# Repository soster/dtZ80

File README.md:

# dtZ80 - A simple 8 Bit Computer based on the Z80 CPU

This started as a project during the second Corona lockdown, where I had to much free time.
I wanted to design my own 8 Bit computer and decided to use the Z80 CPU.
The first idea was to use a MOS 6502 because a variant of that powers the C64, a computer I used much in my childhood.
The Z80 is easier to source where I live so I used that instead.

I started on breadboards but quickly discovered the limits of that so I soldered some prototypes and finally designed some PCBs with kicad.

The bus is compatible to the Bus of the [RC2014 Z80 computer](https://rc2014.co.uk/), so I can exchange expansion cards.

This documentation now covers the new "Black Edition" of the dtZ80 (Rev 1), a larger board without the need to use extension cards. Previous prototypes had a common bus board and extension cards for the CPU, RAM etc. All software for the previous prototypes can be found at `asm/prototype` for historical reasons.

The dtZ80 uses a Z80 CPU with clocked with 7.3728 Mhz (which doubles as a clock for serial communication), a Z80 SIO for serial communication, a CTC counter timer, 32kb of RAM and 32kb of ROM and a AY-3-8910A sound chip. It uses a single seven segment display for debugging purposes and a 4 line, 20 characters per line LCD for text output.

## Tools

* [rasm](https://github.com/mkoloberdin/rasm) is used as the assembler.
* [Visual Studio Code](https://code.visualstudio.com/) is used as an editor and enviroment for assembler
* [Minipro](https://gitlab.com/DavidGriffith/minipro/) is used to flash the EEPROMs, the hardware is a TL866 II PLUS
* [ticks](https://github.com/z88dk/z88dk) from the z88dk project is used as an emulator / simulator
* A usb to ttl converter for serial communication (can be switched to 5V levels, only needs TX and RX)

## Images

### Address Space

Address lines are assigned by a 74LS138 IC (U6) which activates
or deactivates the correct ICs.

    $00: I/O port 7 segment (A0-A7=0)
    $04: LCD command I/O port (A5=1)
    $05: LCD data I/O port (A5=1,A0=1)
    $40: SIO Data Channel A
    $42: SIO Control Channel A
    $60: CTC Channel 0
    $61: CTC Channel 1
    $62: CTC Channel 2
    $63: CTC Channel 3
    $80: Sound Register
    $81: Sound Data

#### LCD

The black edition uses a 4 line, 20 column LCD Display (2004A V1.1) probably based on the HD44780 Chip [(Datasheet)](https://www.sparkfun.com/datasheets/LCD/HD44780.pdf).
It behaves strangely if we send character by character to it, it uses line 3 after line 1 and the lines 2 and 4 are not usable. We have to manually set the DDRAM address holding the character position according to the current line:

    Line 1: $00 - $13
    Line 2: $40 - $53
    Line 3: $14 - $27
    Line 4: $54 - $67

I assume this is due to backwarts compatibility to 2 line displays.

#### Parallel Interface

The 8 Bit parallel Interface is used to connect a lcd screen mainly. Due to an error while designing the pcb, it has the following pins (GND=Pin 1):

#### Serial Interface

The serial interface is provided by the Z80 SIO chip (SI0/0). It has two channels, A (J1) and B (J6). The clock is provided by the CTC chip for channel A. If you want to use channel B, you have to connect the clock from the pin CTS from J1 to CTS on J6. Please note that RX and TX are labeled from the point of view of the external device, RX is connected to TX on the SIO and vice versa (this maybe was a stupid decistion).

If you are working with linux and you have a usb to serial converter connected to /dev/ttyUSB0 you can use `screen` to enter serial terminal mode:

    screen /dev/ttyUSB0 19200

To enter serial mode of the dtZ80 simply press enter now.

Screen commands consist of "C-a" or ctrl+a (holding down the control key, and then pressing the 'a' key, then releasing both), to enter the command input mode, then commands may be entered with another key stroke.
To disconnect from the session: Ctrl+a, Ctrl+d, you can then use this to reattach to the session:

    screen -r

To quit screen and close connection: ctrl+a, k.

### CTC Clock Timer Chip

TODO

### PS/2 Keyboard module

For ps/2 keyboard to serial conversion I use a "PS2 Keyboard Driver Serial Port Transmission Module".
 
1. connect TX from the module to TX from J1. The module communicates via serial in 19.200 Baud, 1 Stop bit, no parity.

### Sound

TODO

### Simulator / Emulator

The simulator `ticks` from [https://github.com/z88dk/z88dk](https://github.com/z88dk/z88dk) can be used as a simulator. It provides character output for debugging purposes. Use it like this on assembled binary files:

```
z88dk.z88dk-ticks -iochar 5 bios.bin
```
`-iochar 5` puts out characters just like for the LCD of the dtz80.

## Next steps / TODOs

* Further develop the bios
* Tiny Basic example code: http://cpuville.com/Code/tinybasic2dms_asm.txt
* Document all features

### Graphics

Graphics is not finished yet. These are some ideas:
Based on: TMS9918A
Problem: Works only with DRAM for SRAM
Looks like you will need to latch the address bits 8-15 when RAS goes low
Connect (/CAS0 AND /CAS1) to /OE on the SRAM and use one of them for A16 also
Important: Clock 10.738635 Mhz, Type ‎MP107-E‎ for video timing
Use schematics from: https://github.com/jblang/TMS9918A

## Links
* [Bread 80](https://bread80.com/) A Z80 on breadboards
* [RC2014](https://rc2014.co.uk/) Another Z80 project
* [LM80C Color Computer](https://hackaday.io/project/165246-lm80c-color-computer) Another Z80 Computer, interesting because of graphics output
* [Z80 Assembler for dummies](https://www.msx.org/wiki/Z80_Assembler_for_Dummies) Z80 Assembler Guide

## More images

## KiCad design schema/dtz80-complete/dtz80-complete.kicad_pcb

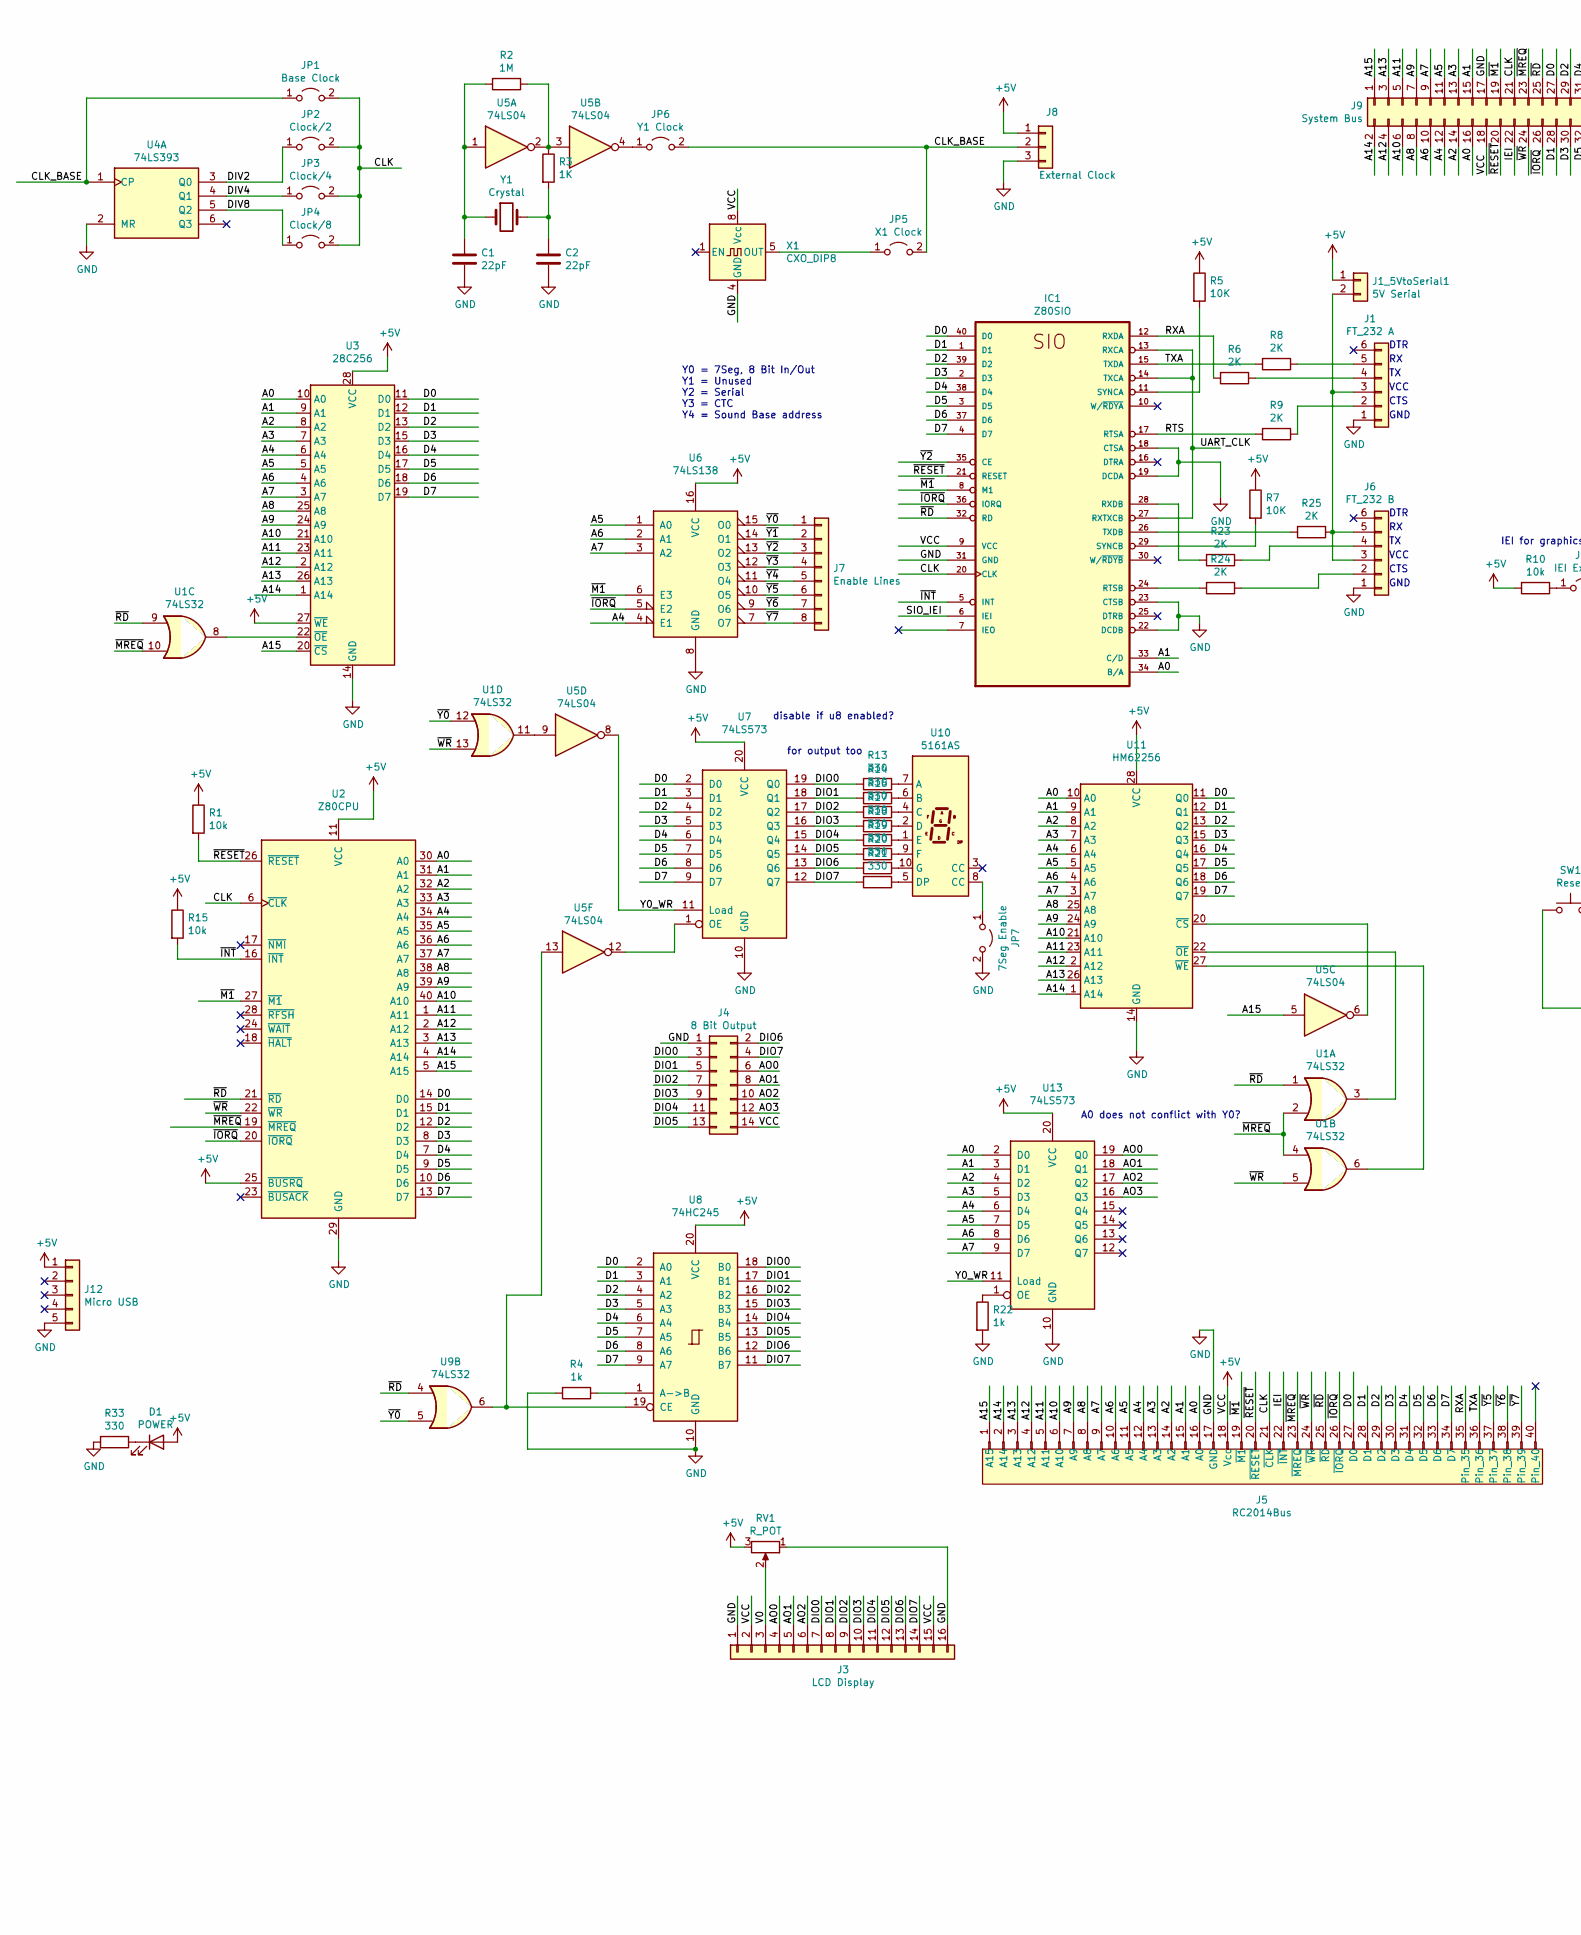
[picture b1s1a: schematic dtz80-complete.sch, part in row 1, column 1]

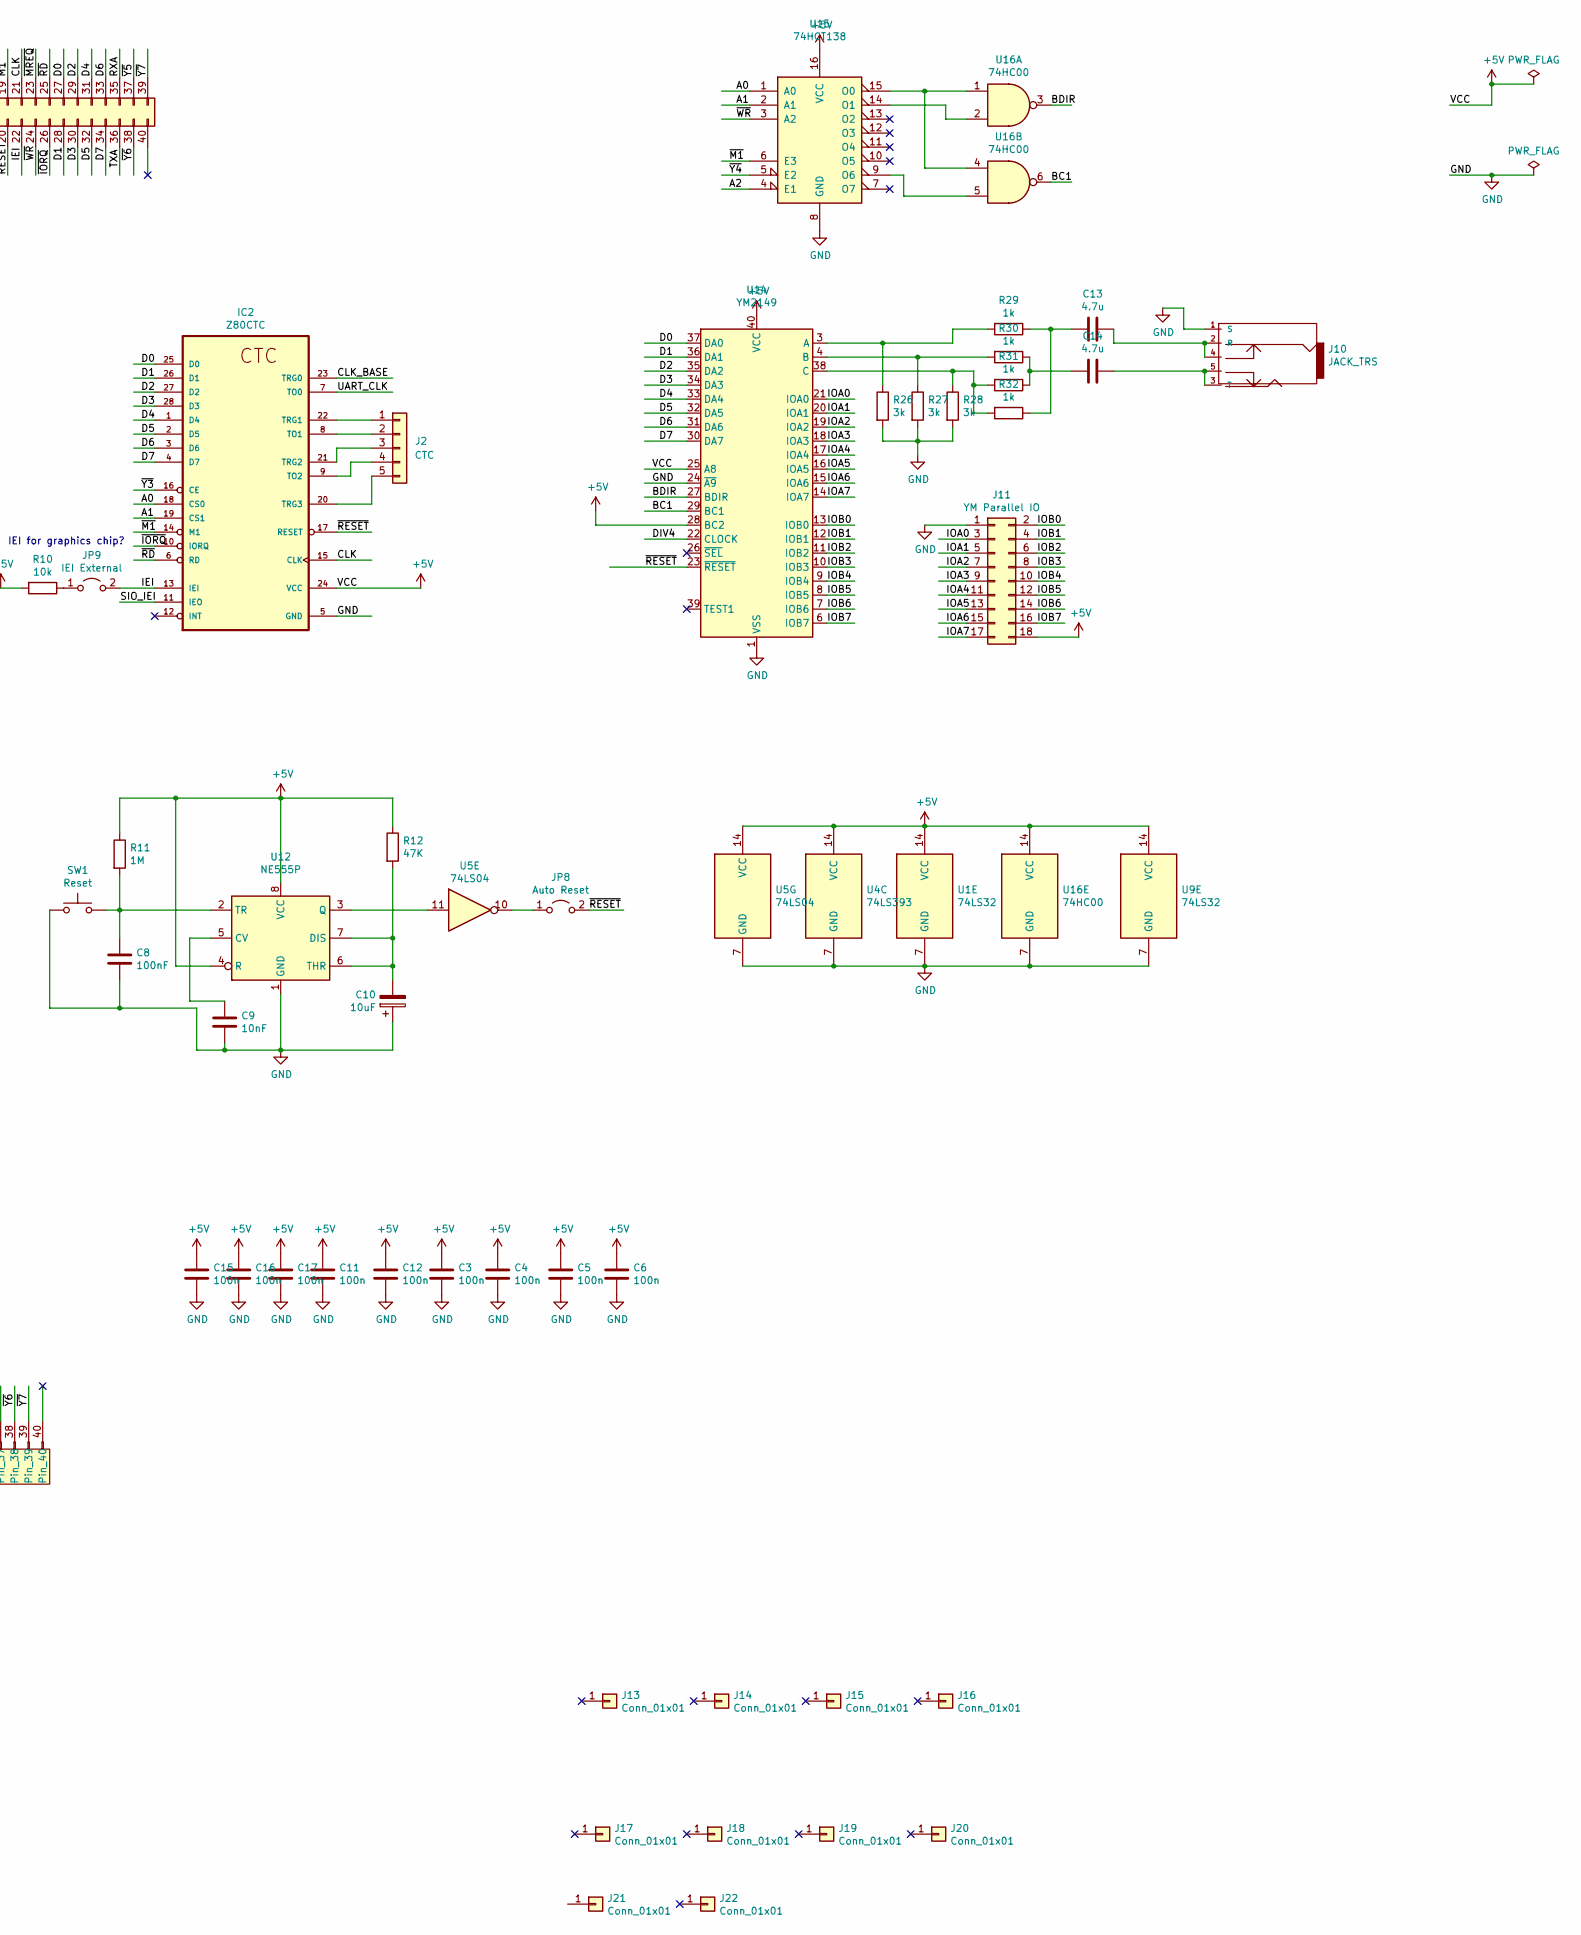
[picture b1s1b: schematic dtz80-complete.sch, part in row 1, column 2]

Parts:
C1, C2: 22pF; C_Disc_D4.3mm_W1.9mm_P5.00mm
C3, C4, C5, C6, C11, C12, C15, C16, C17: 100n; C_Disc_D4.3mm_W1.9mm_P5.00mm
C8: 100nF; C_Disc_D4.3mm_W1.9mm_P5.00mm
C9: 10nF; C_Disc_D4.3mm_W1.9mm_P5.00mm
C10: 10uF; C_Disc_D4.3mm_W1.9mm_P5.00mm
C13, C14: 4.7u; C_Radial_D6.3mm_H5.0mm_P2.50mm
D1: POWER; LED_D3.0mm
IC1: Z80SIO; DIP-40_W15.24mm_Socket
IC2: Z80CTC; DIP-28_W15.24mm_Socket
J1: FT_232 A; PinHeader_1x06_P2.54mm_Vertical
J1_5VtoSerial1: 5V Serial; PinHeader_1x02_P2.54mm_Vertical
J2: CTC; PinHeader_1x05_P2.54mm_Vertical
J3: LCD Display; PinHeader_1x16_P2.54mm_Vertical
J4: 8 Bit Output; PinHeader_2x07_P2.54mm_Vertical
J5: RC2014Bus; PinHeader_1x40_P2.54mm_Vertical
J6: FT_232 B; PinHeader_1x06_P2.54mm_Vertical
J7: Enable Lines; PinHeader_1x08_P2.54mm_Vertical
J8: External Clock; PinHeader_1x03_P2.54mm_Vertical
J9: System Bus; PinHeader_2x20_P2.54mm_Vertical
J10: JACK_TRS; Tayda_3.5mm_stereo_TRS_jack_A-853
J11: YM Parallel IO; PinHeader_2x09_P2.54mm_Vertical
J12: Micro USB; PinHeader_1x05_P2.54mm_Vertical
J13, J14, J15, J16, J17, J18, J19, J20, J21, J22: Conn_01x01; MountingHole_3.2mm_M3_DIN965_Pad
JP1: Base Clock; PinHeader_1x02_P2.54mm_Vertical
JP2: Clock/2; PinHeader_1x02_P2.54mm_Vertical
JP3: Clock/4; PinHeader_1x02_P2.54mm_Vertical
JP4: Clock/8; PinHeader_1x02_P2.54mm_Vertical
JP5: X1 Clock; PinHeader_1x02_P2.54mm_Vertical
JP6: Y1 Clock; PinHeader_1x02_P2.54mm_Vertical
JP7: 7Seg Enable; PinHeader_1x02_P2.54mm_Vertical
JP8: Auto Reset; PinHeader_1x02_P2.54mm_Vertical
JP9: IEI External; PinHeader_1x02_P2.54mm_Vertical
R1, R10, R15: 10k; R_Axial_DIN0207_L6.3mm_D2.5mm_P10.16mm_Horizontal
R2, R11: 1M; R_Axial_DIN0207_L6.3mm_D2.5mm_P10.16mm_Horizontal
R3: 1K; R_Axial_DIN0207_L6.3mm_D2.5mm_P10.16mm_Horizontal
R4, R22, R29, R30, R31, R32: 1k; R_Axial_DIN0207_L6.3mm_D2.5mm_P10.16mm_Horizontal
R5, R7: 10K; R_Axial_DIN0207_L6.3mm_D2.5mm_P10.16mm_Horizontal
R6, R8, R9, R23, R24, R25: 2K; R_Axial_DIN0207_L6.3mm_D2.5mm_P10.16mm_Horizontal
R12: 47K; R_Axial_DIN0207_L6.3mm_D2.5mm_P10.16mm_Horizontal
R13, R14, R16, R17, R18, R19, R20, R21, R33: 330; R_Axial_DIN0207_L6.3mm_D2.5mm_P10.16mm_Horizontal
R26, R27, R28: 3k; R_Axial_DIN0207_L6.3mm_D2.5mm_P10.16mm_Horizontal
RV1: R_POT; Potentiometer_ACP_CA9-V10_Vertical
SW1: Reset; SW_TH_Tactile_Omron_B3F-10xx
U1, U9: 74LS32; DIP-14_W7.62mm_Socket
U2: Z80CPU; DIP-40_W15.24mm_Socket
U3: 28C256; DIP-28_W15.24mm_Socket_Large_Holes
U4: 74LS393; DIP-14_W7.62mm_Socket
U5: 74LS04; DIP-14_W7.62mm_Socket
U6: 74LS138; DIP-16_W7.62mm_Socket
U7, U13: 74LS573; DIP-20_W7.62mm_Socket
U8: 74HC245; DIP-20_W7.62mm_Socket
U10: 5161AS; 7SegmentLED_LTS6760_LTS6780
U11: HM62256; DIP-28_W15.24mm_Socket
U12: NE555P; DIP-8_W7.62mm
U14: YM2149; DIP-40_W15.24mm_Socket
U15: 74HCT138; DIP-16_W7.62mm_Socket
U16: 74HC00; DIP-14_W7.62mm_Socket
X1: CXO_DIP8; Oscillator_DIP-8
Y1: Crystal; Crystal_HC52-8mm_Vertical

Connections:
+5V: C3.1, C4.1, C5.1, C6.1, C11.1, C12.1, C15.1, C16.1, C17.1, D1.2 (A), IC1.9 (VCC), IC2.24 (VCC), J1_5VtoSerial1.1, J3.2, J3.15, J4.14, J5.18 (Vcc), J8.1, J9.18, J11.18, J12.1, R1.1, R5.1, R7.1, R10.2, R11.1, R12.1, R15.1, RV1.3, U1.14 (VCC), U2.11 (VCC), U2.25 (~BUSRQ~), U3.27 (~WE), U3.28 (VCC), U4.14 (VCC), U5.14 (VCC), U6.16 (VCC), U7.20 (VCC), U8.20 (VCC), U9.14 (VCC), U11.28 (VCC), U12.4 (R), U12.8 (VCC), U13.20 (VCC), U14.25 (A8), U14.28 (BC2), U14.40 (VCC), U15.16 (VCC), U16.14 (VCC), X1.8 (Vcc); also elsewhere on the board
/A0: IC1.34 (B/A), IC2.18 (CS0), J5.16 (A0), J9.16, U2.30 (A0), U3.10 (A0), U11.10 (A0), U13.2 (D0), U15.1 (A0)
/A1: IC1.33 (C/D), IC2.19 (CS1), J5.15 (A1), J9.15, U2.31 (A1), U3.9 (A1), U11.9 (A1), U13.3 (D1), U15.2 (A1)
/A2: J5.14 (A2), J9.14, U2.32 (A2), U3.8 (A2), U11.8 (A2), U13.4 (D2), U15.4 (E1)
/A3: J5.13 (A3), J9.13, U2.33 (A3), U3.7 (A3), U11.7 (A3), U13.5 (D3)
/A4: J5.12 (A4), J9.12, U2.34 (A4), U3.6 (A4), U6.4 (E1), U11.6 (A4), U13.6 (D4)
/A5: J5.11 (A5), J9.11, U2.35 (A5), U3.5 (A5), U6.1 (A0), U11.5 (A5), U13.7 (D5)
/A6: J5.10 (A6), J9.10, U2.36 (A6), U3.4 (A6), U6.2 (A1), U11.4 (A6), U13.8 (D6)
/A7: J5.9 (A7), J9.9, U2.37 (A7), U3.3 (A7), U6.3 (A2), U11.3 (A7), U13.9 (D7)
/A8: J5.8 (A8), J9.8, U2.38 (A8), U3.25 (A8), U11.25 (A8)
/A9: J5.7 (A9), J9.7, U2.39 (A9), U3.24 (A9), U11.24 (A9)
/A10: J5.6 (A10), J9.6, U2.40 (A10), U3.21 (A10), U11.21 (A10)
/A11: J5.5 (A11), J9.5, U2.1 (A11), U3.23 (A11), U11.23 (A11)
/A12: J5.4 (A12), J9.4, U2.2 (A12), U3.2 (A12), U11.2 (A12)
/A13: J5.3 (A13), J9.3, U2.3 (A13), U3.26 (A13), U11.26 (A13)
/A14: J5.2 (A14), J9.2, U2.4 (A14), U3.1 (A14), U11.1 (A14)
/AO0: J3.4, J4.6, U13.19 (Q0)
/AO1: J3.5, J4.8, U13.18 (Q1)
/AO2: J3.6, J4.10, U13.17 (Q2)
/AO3: J4.12, U13.16 (Q3)
/BC1: U14.29 (BC1), U16.6
/BDIR: U14.27 (BDIR), U16.3
/CLK: IC1.20 (CLK), IC2.15 (CLK), J5.21 (~CLK~), J9.21, JP1.2 (B), JP2.2 (B), JP3.2 (B), JP4.2 (B), U2.6 (~CLK~)
/CLK_BASE: IC2.23 (TRG0), J8.2, JP1.1 (A), JP5.2 (B), JP6.2 (B), U4.1 (CP)
/D0: IC1.40 (D0), IC2.25 (D0), J5.27 (D0), J9.27, U2.14 (D0), U3.11 (D0), U7.2 (D0), U8.2 (A0), U11.11 (Q0), U14.37 (DA0)
/D1: IC1.1 (D1), IC2.26 (D1), J5.28 (D1), J9.28, U2.15 (D1), U3.12 (D1), U7.3 (D1), U8.3 (A1), U11.12 (Q1), U14.36 (DA1)
/D2: IC1.39 (D2), IC2.27 (D2), J5.29 (D2), J9.29, U2.12 (D2), U3.13 (D2), U7.4 (D2), U8.4 (A2), U11.13 (Q2), U14.35 (DA2)
/D3: IC1.2 (D3), IC2.28 (D3), J5.30 (D3), J9.30, U2.8 (D3), U3.15 (D3), U7.5 (D3), U8.5 (A3), U11.15 (Q3), U14.34 (DA3)
/D4: IC1.38 (D4), IC2.1 (D4), J5.31 (D4), J9.31, U2.7 (D4), U3.16 (D4), U7.6 (D4), U8.6 (A4), U11.16 (Q4), U14.33 (DA4)
/D5: IC1.3 (D5), IC2.2 (D5), J5.32 (D5), J9.32, U2.9 (D5), U3.17 (D5), U7.7 (D5), U8.7 (A5), U11.17 (Q5), U14.32 (DA5)
/D6: IC1.37 (D6), IC2.3 (D6), J5.33 (D6), J9.33, U2.10 (D6), U3.18 (D6), U7.8 (D6), U8.8 (A6), U11.18 (Q6), U14.31 (DA6)
/D7: IC1.4 (D7), IC2.4 (D7), J5.34 (D7), J9.34, U2.13 (D7), U3.19 (D7), U7.9 (D7), U8.9 (A7), U11.19 (Q7), U14.30 (DA7)
/DIO0: J3.7, J4.3, R13.2, U7.19 (Q0), U8.18 (B0)
/DIO1: J3.8, J4.5, R14.2, U7.18 (Q1), U8.17 (B1)
/DIO2: J3.9, J4.7, R16.2, U7.17 (Q2), U8.16 (B2)
/DIO3: J3.10, J4.9, R17.2, U7.16 (Q3), U8.15 (B3)
/DIO4: J3.11, J4.11, R18.2, U7.15 (Q4), U8.14 (B4)
/DIO5: J3.12, J4.13, R19.2, U7.14 (Q5), U8.13 (B5)
/DIO6: J3.13, J4.2, R20.2, U7.13 (Q6), U8.12 (B6)
/DIO7: J3.14, J4.4, R21.2, U7.12 (Q7), U8.11 (B7)
/DIV2: JP2.1 (A), U4.3 (Q0)
/DIV4: JP3.1 (A), U4.4 (Q1), U14.22 (CLOCK)
/DIV8: JP4.1 (A), U4.5 (Q2)
/IEI: IC2.13 (IEI), J5.22 (~INT~), J9.22, JP9.2 (B)
/IOA0: J11.3, U14.21 (IOA0)
/IOA1: J11.5, U14.20 (IOA1)
/IOA2: J11.7, U14.19 (IOA2)
/IOA3: J11.9, U14.18 (IOA3)
/IOA4: J11.11, U14.17 (IOA4)
/IOA5: J11.13, U14.16 (IOA5)
/IOA6: J11.15, U14.15 (IOA6)
/IOA7: J11.17, U14.14 (IOA7)
/IOB0: J11.2, U14.13 (IOB0)
/IOB1: J11.4, U14.12 (IOB1)
/IOB2: J11.6, U14.11 (IOB2)
/IOB3: J11.8, U14.10 (IOB3)
/IOB4: J11.10, U14.9 (IOB4)
/IOB5: J11.12, U14.8 (IOB5)
/IOB6: J11.14, U14.7 (IOB6)
/IOB7: J11.16, U14.6 (IOB7)
/RTS: IC1.17 (RTSA), R9.2
/SIO_IEI: IC1.6 (IEI), IC2.11 (IEO)
/UART_CLK: IC1.13 (RXCA), IC1.14 (TXCA), IC1.27 (RXTXCB), IC2.7 (TO0)
/V0: J3.3, RV1.2
/Y0_WR: U5.8, U7.11 (Load), U13.11 (Load)
/~INT~: IC1.5 (INT), R15.2, U2.16 (~INT~)
/~IORQ~: IC1.36 (IORQ), IC2.10 (IORQ), J5.26 (~IORQ~), J9.26, U2.20 (~IORQ~), U6.5 (E2)
/~M1~: IC1.8 (M1), IC2.14 (M1), J5.19 (~M1~), J9.19, U2.27 (~M1~), U6.6 (E3), U15.6 (E3)
/~MREQ~: J5.23 (~MREQ~), J9.23, U1.2, U1.4, U1.10, U2.19 (~MREQ~)
/~RD~: IC1.32 (RD), IC2.6 (RD), J5.25 (~RD~), J9.25, U1.1, U1.9, U2.21 (~RD~), U9.4
/~RESET~: IC1.21 (RESET), IC2.17 (RESET), J5.20 (~RESET~), J9.20, JP8.2 (B), R1.2, U2.26 (~RESET~), U14.23 (~RESET)
/~WR~: J5.24 (~WR~), J9.24, U1.5, U1.13, U2.22 (~WR~), U15.3 (A2)
/~Y0~: J7.1, U1.12, U6.15 (O0), U9.5
/~Y1~: J7.2, U6.14 (O1)
/~Y2~: IC1.35 (CE), J7.3, U6.13 (O2)
/~Y3~: IC2.16 (CE), J7.4, U6.12 (O3)
/~Y4~: J7.5, U6.11 (O4), U15.5 (E2)
/~Y5~: J5.37, J7.6, J9.37, U6.10 (O5)
/~Y6~: J5.38, J7.7, J9.38, U6.9 (O6)
/~Y7~: J5.39, J7.8, J9.39, U6.7 (O7)
GND: C1.2, C2.2, C3.2, C4.2, C5.2, C6.2, C8.2, C9.2, C10.1, C11.2, C12.2, C15.2, C16.2, C17.2, IC1.18 (CTSA), IC1.19 (DCDA), IC1.22 (DCDB), IC1.23 (CTSB), IC1.31 (GND), IC2.5 (GND), J1.1, J3.1, J3.16, J4.1, J5.17 (GND), J6.1, J8.3, J9.17, J10.1 (S), J11.1, J12.5, JP7.2 (B), R4.2, R22.2, R26.2, R27.2, R28.2, R33.2, RV1.1, SW1.1 (A), SW1.2 (A), U1.7 (GND), U2.29 (GND), U3.14 (GND), U4.2 (MR), U4.7 (GND), U5.7 (GND), U6.8 (GND), U7.10 (GND), U8.10 (GND), U9.7 (GND), U11.14 (GND), U12.1 (GND), U13.10 (GND), U14.1 (VSS), U14.24 (~A9), U15.8 (GND), U16.7 (GND), X1.4 (GND)
unnamed: C1.1, R2.2, U5.1, Y1.1
unnamed: C2.1, R3.2, Y1.2
unnamed: C8.1, R11.2, SW1.3 (B), SW1.4 (B), U12.2 (TR)
unnamed: C9.1, U12.5 (CV)
unnamed: C10.2, R12.2, U12.6 (THR), U12.7 (DIS)
unnamed: C13.1, J10.2 (R), J10.4
unnamed: C13.2, R29.1, R32.1
unnamed: C14.1, J10.3 (T), J10.5
unnamed: C14.2, R30.1, R31.1
unnamed: D1.1 (K), R33.1
unnamed: IC1.11 (SYNCA), R5.2
unnamed: IC1.24 (RTSB), R24.2
unnamed: IC1.26 (TXDB), R25.2
unnamed: IC1.28 (RXDB), R23.2
unnamed: IC1.29 (SYNCB), R7.2
unnamed: IC2.8 (TO1), J2.2
unnamed: IC2.9 (TO2), J2.4
unnamed: IC2.20 (TRG3), J2.5
unnamed: IC2.21 (TRG2), J2.3
unnamed: IC2.22 (TRG1), J2.1
unnamed: J1.2, R9.1
unnamed: J1.3, J1_5VtoSerial1.2, J6.3, J6.5, R25.1
unnamed: J1.4, R6.1
unnamed: J1.5, R8.1
unnamed: J6.2, R24.1
unnamed: J6.4, R23.1
unnamed: JP5.1 (A), X1.5 (OUT)
unnamed: JP6.1 (A), U5.4
unnamed: JP7.1 (A), U10.8 (CC)
unnamed: JP8.1 (A), U5.10
unnamed: JP9.1 (A), R10.1
unnamed: R2.1, R3.1, U5.2, U5.3
unnamed: R4.1, U8.1 (A->B)
unnamed: R13.1, U10.7 (A)
unnamed: R14.1, U10.6 (B)
unnamed: R16.1, U10.4 (C)
unnamed: R17.1, U10.2 (D)
unnamed: R18.1, U10.1 (E)
unnamed: R19.1, U10.9 (F)
unnamed: R20.1, U10.10 (G)
unnamed: R21.1, U10.5 (DP)
unnamed: R22.1, U13.1 (OE)
unnamed: R26.1, R29.2, U14.3 (A)
unnamed: R27.1, R30.2, U14.4 (B)
unnamed: R28.1, R31.2, R32.2, U14.38 (C)
unnamed: U1.3, U11.22 (~OE)
unnamed: U1.6, U11.27 (~WE)
unnamed: U1.8, U3.22 (~OE)
unnamed: U1.11, U5.9
unnamed: U5.12, U7.1 (OE)
unnamed: U5.13, U8.19 (CE), U9.6
unnamed: U5.6, U11.20 (~CS)
unnamed: U5.11, U12.3 (Q)
unnamed: U15.9 (O6), U16.5
unnamed: U15.14 (O1), U16.2
unnamed: U15.15 (O0), U16.1, U16.4

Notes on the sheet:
Y0 = 7Seg, 8 Bit In/Out Y1 = Unused Y2 = Serial Y3 = CTC Y4 = Sound Base address
DTR
VCC
CTS
GND
for output too
IEI for graphics chip?
disable if u8 enabled?
A0 does not conflict with Y0?

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
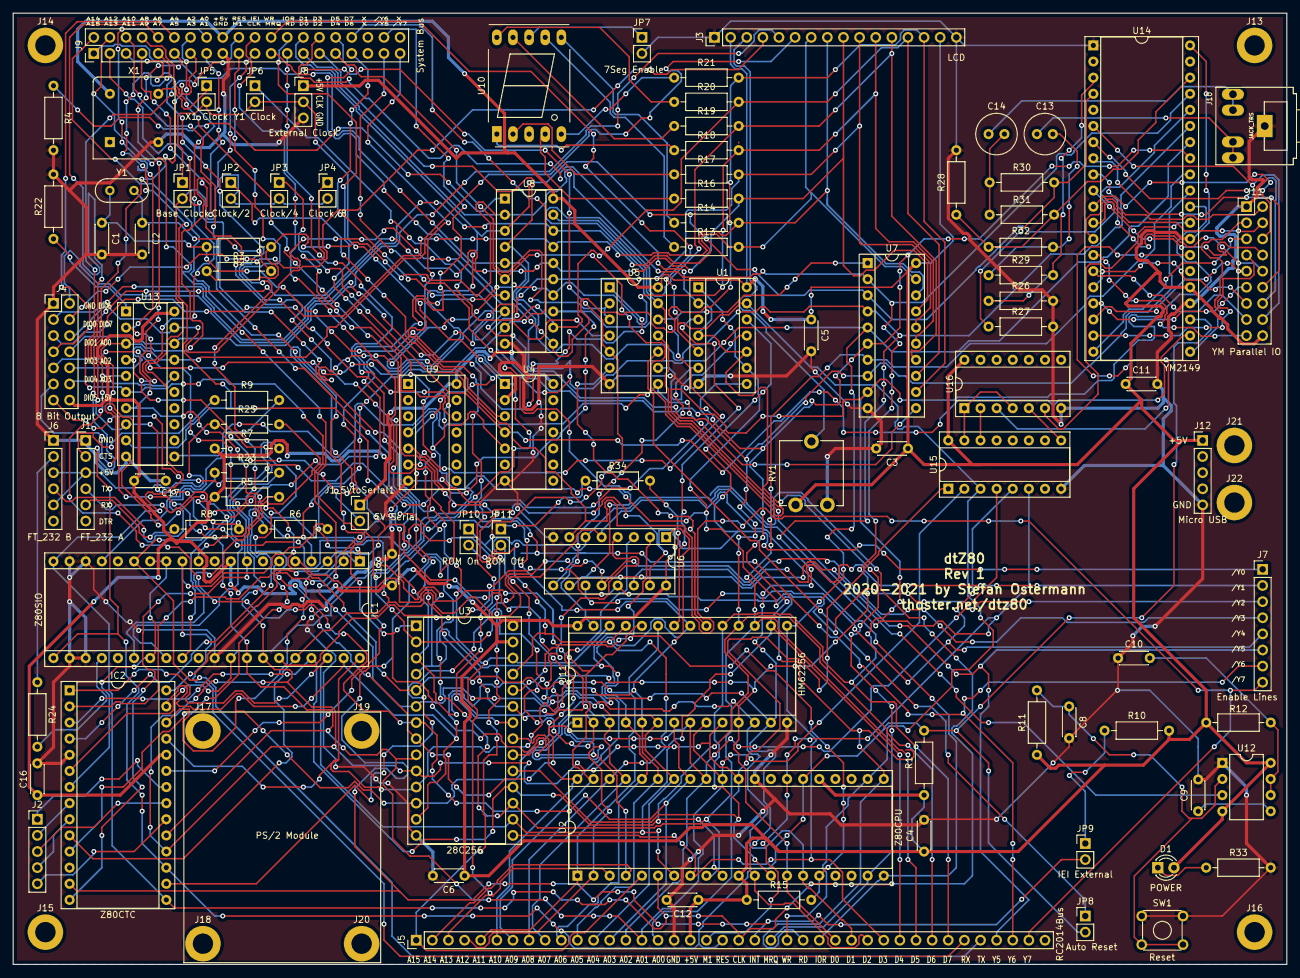
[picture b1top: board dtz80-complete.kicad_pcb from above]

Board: 2 copper layers, 200.7 x 149.9 mm, 107 parts (0 on the bottom side), 142 nets.

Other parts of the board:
JP10: ROM On; PinHeader_1x02_P2.54mm_Vertical
JP11: ROM Off; PinHeader_1x02_P2.54mm_Vertical
R34: 10k; R_Axial_DIN0207_L6.3mm_D2.5mm_P10.16mm_Horizontal

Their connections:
+5V: R34.2; also elsewhere on the board
unnamed: JP11.1, R34.1

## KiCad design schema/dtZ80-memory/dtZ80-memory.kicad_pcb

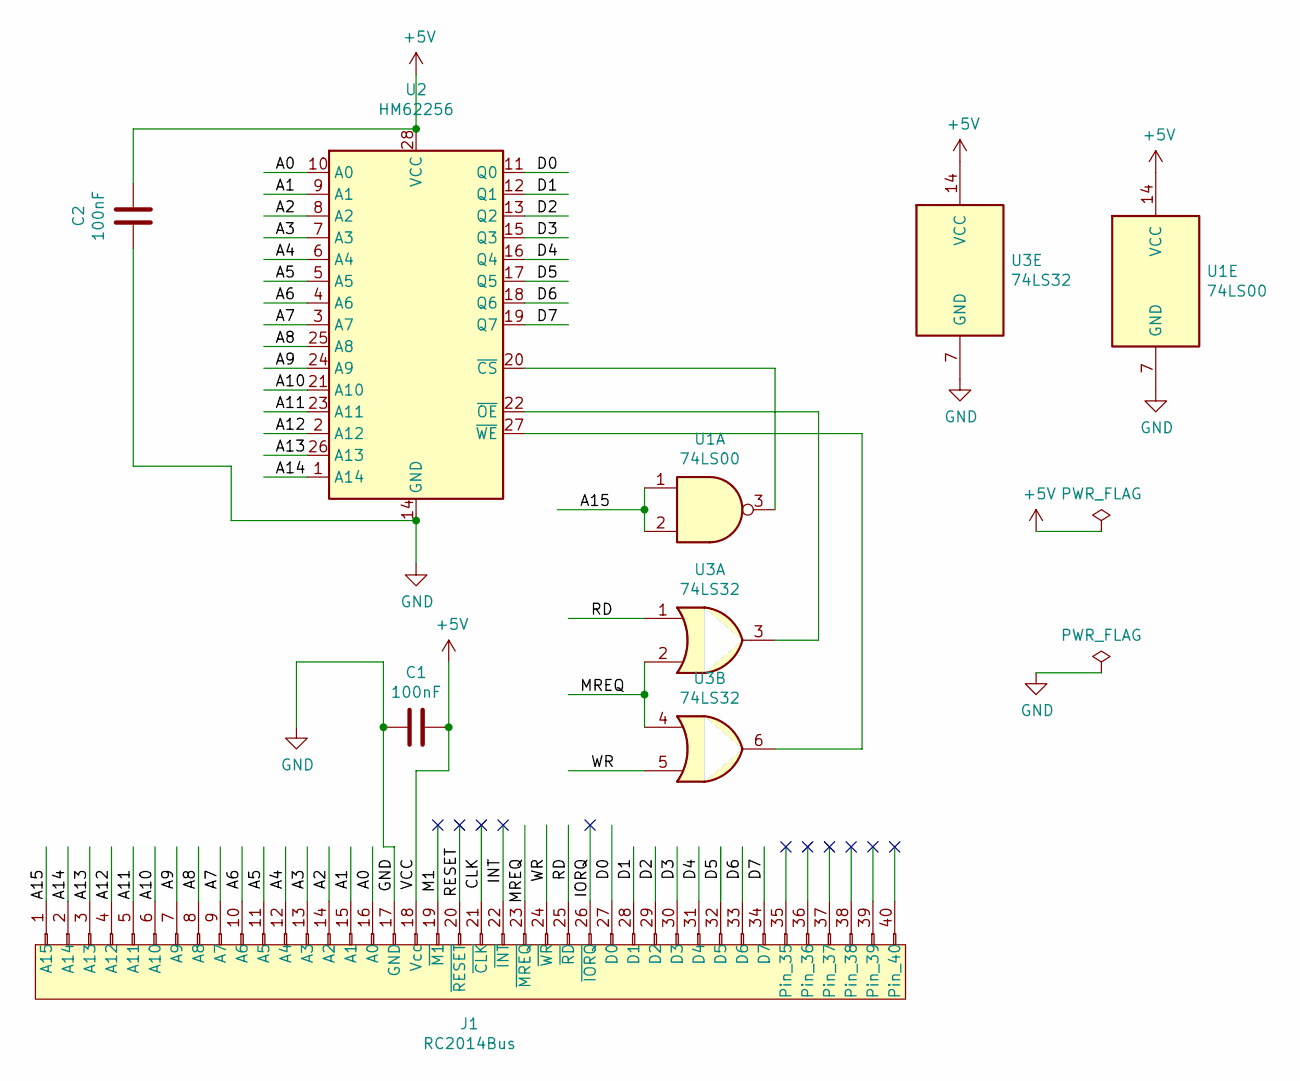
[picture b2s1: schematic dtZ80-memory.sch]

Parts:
C1, C2: 100nF; C_Disc_D3.0mm_W2.0mm_P2.50mm
J1: RC2014Bus
U1: 74LS00; DIP-14_W7.62mm_Socket
U2: HM62256; DIP-28_W15.24mm_Socket
U3: 74LS32; DIP-14_W7.62mm_Socket

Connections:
+5V: C1.1, C2.1, J1.18 (Vcc), U1.14 (VCC), U2.28 (VCC), U3.14 (VCC)
/A0: J1.16 (A0), U2.10 (A0)
/A1: J1.15 (A1), U2.9 (A1)
/A2: J1.14 (A2), U2.8 (A2)
/A3: J1.13 (A3), U2.7 (A3)
/A4: J1.12 (A4), U2.6 (A4)
/A5: J1.11 (A5), U2.5 (A5)
/A6: J1.10 (A6), U2.4 (A6)
/A7: J1.9 (A7), U2.3 (A7)
/A8: J1.8 (A8), U2.25 (A8)
/A9: J1.7 (A9), U2.24 (A9)
/A10: J1.6 (A10), U2.21 (A10)
/A11: J1.5 (A11), U2.23 (A11)
/A12: J1.4 (A12), U2.2 (A12)
/A13: J1.3 (A13), U2.26 (A13)
/A14: J1.2 (A14), U2.1 (A14)
/A15: J1.1 (A15), U1.1, U1.2
/CLK: J1.21 (~CLK~)
/D0: J1.27 (D0), U2.11 (Q0)
/D1: J1.28 (D1), U2.12 (Q1)
/D2: J1.29 (D2), U2.13 (Q2)
/D3: J1.30 (D3), U2.15 (Q3)
/D4: J1.31 (D4), U2.16 (Q4)
/D5: J1.32 (D5), U2.17 (Q5)
/D6: J1.33 (D6), U2.18 (Q6)
/D7: J1.34 (D7), U2.19 (Q7)
/INT: J1.22 (~INT~)
/IORQ: J1.26 (~IORQ~)
/M1: J1.19 (~M1~)
/MREQ: J1.23 (~MREQ~), U3.2, U3.4
/RD: J1.25 (~RD~), U3.1
/RESET: J1.20 (~RESET~)
/WR: J1.24 (~WR~), U3.5
GND: C1.2, C2.2, J1.17 (GND), U1.7 (GND), U2.14 (GND), U3.7 (GND)
unnamed: U1.3, U2.20 (~CS)
unnamed: U2.22 (~OE), U3.3
unnamed: U2.27 (~WE), U3.6

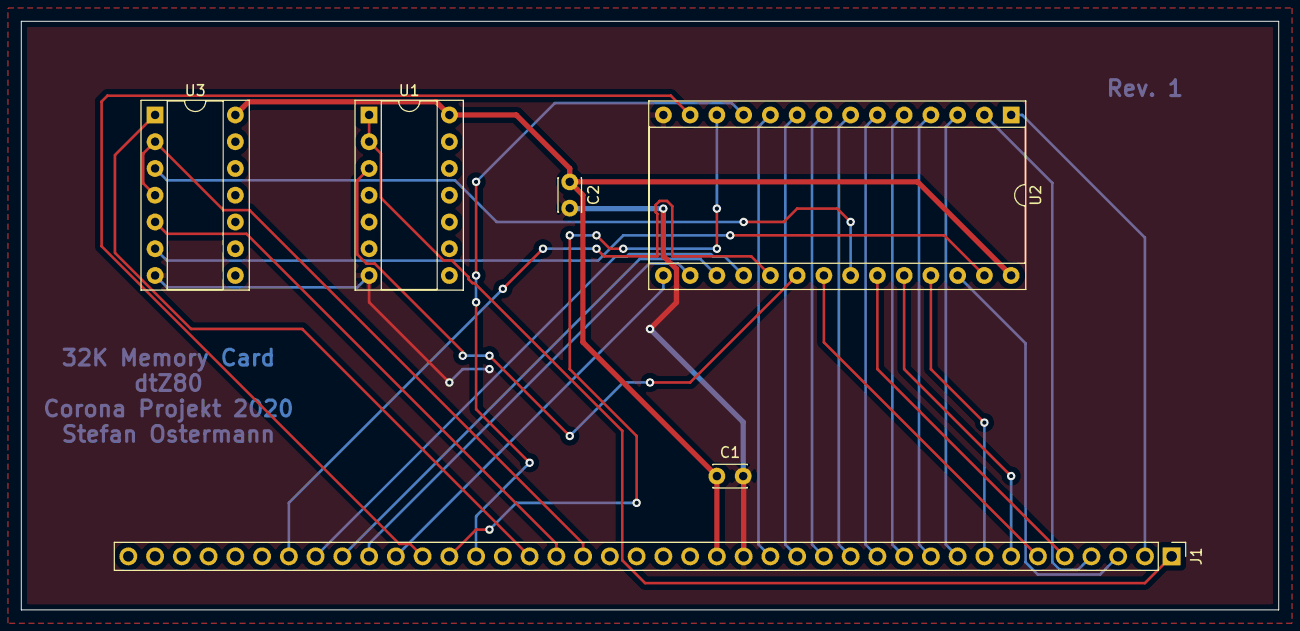
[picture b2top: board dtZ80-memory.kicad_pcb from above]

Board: 2 copper layers, 119.4 x 55.9 mm, 6 parts (0 on the bottom side), 32 nets.
